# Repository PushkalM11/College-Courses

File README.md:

# College-Courses
Repository to store courses I have done at IIT Hyderabad during BTech.

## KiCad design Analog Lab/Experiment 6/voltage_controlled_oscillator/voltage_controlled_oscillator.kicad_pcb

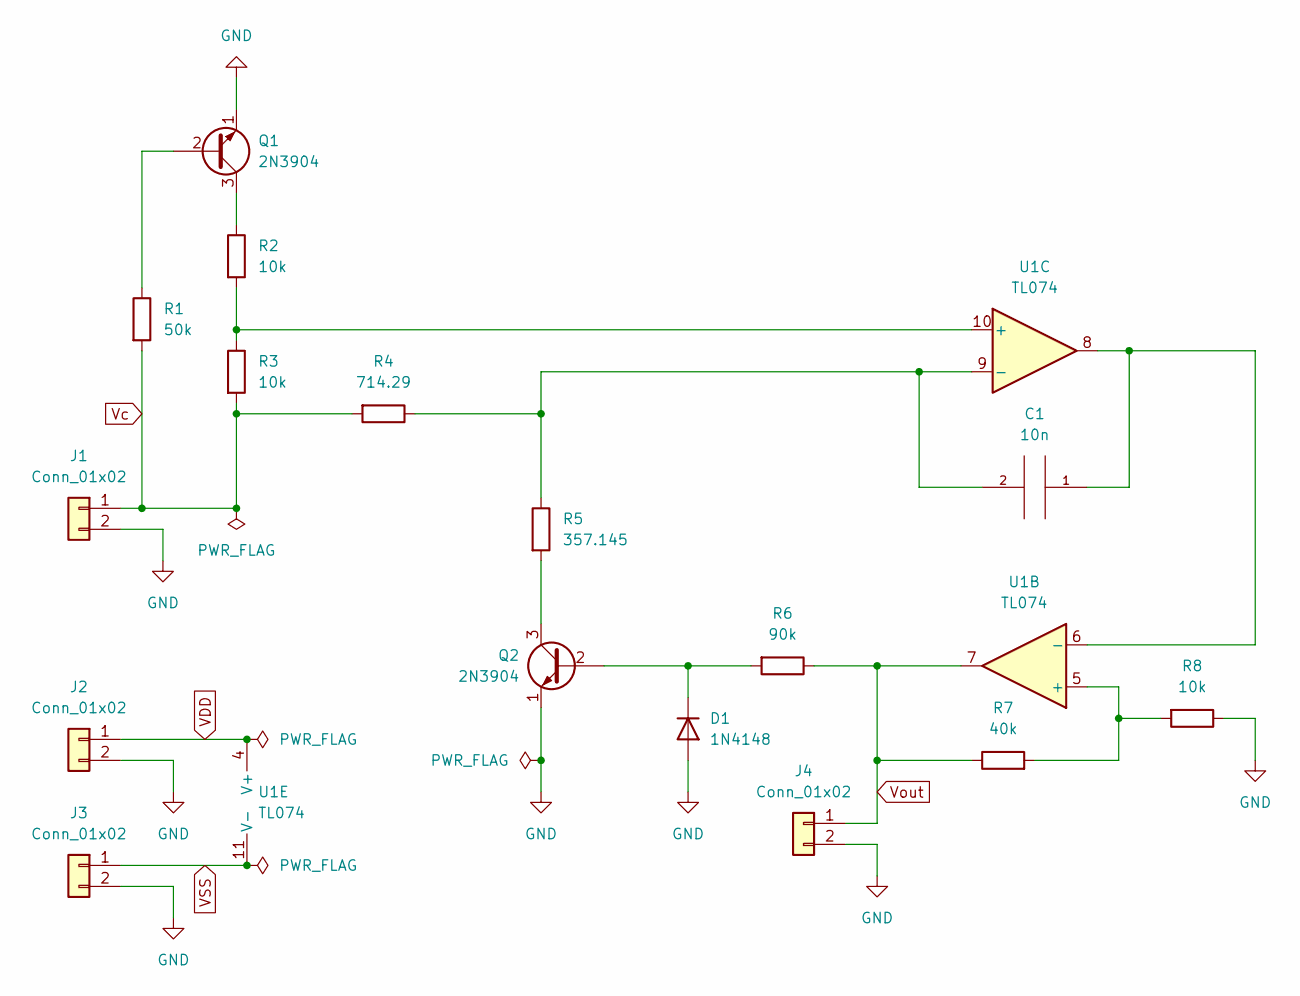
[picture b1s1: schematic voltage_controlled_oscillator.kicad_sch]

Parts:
C1: 10n; C_Disc_D3.4mm_W2.1mm_P2.50mm
D1: 1N4148; D_DO-35_SOD27_P7.62mm_Horizontal
J1, J2, J3, J4: Conn_01x02; Banana_Jack_2Pin
Q1, Q2: 2N3904; TO-92_Wide
R1: 50k; R_Axial_DIN0204_L3.6mm_D1.6mm_P1.90mm_Vertical
R2, R3, R8: 10k; R_Axial_DIN0204_L3.6mm_D1.6mm_P1.90mm_Vertical
R4: 714.29; R_Axial_DIN0204_L3.6mm_D1.6mm_P1.90mm_Vertical
R5: 357.145; R_Axial_DIN0204_L3.6mm_D1.6mm_P1.90mm_Vertical
R6: 90k; R_Axial_DIN0204_L3.6mm_D1.6mm_P1.90mm_Vertical
R7: 40k; R_Axial_DIN0204_L3.6mm_D1.6mm_P1.90mm_Vertical
U1: TL074; DIP-14_W7.62mm_LongPads

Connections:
GND: D1.2 (A), J1.2, J2.2, J3.2, J4.2, Q1.1 (E), Q2.1 (E), R8.1
unnamed: C1.1, U1.6 (-), U1.8
unnamed: C1.2, R4.1, R5.1, U1.9 (-)
unnamed: D1.1 (K), Q2.2 (B), R6.2
unnamed: Q1.2 (B), R1.1
unnamed: Q1.3 (C), R2.1
unnamed: Q2.3 (C), R5.2
unnamed: R2.2, R3.1, U1.10 (+)
unnamed: R7.2, R8.2, U1.5 (+)
VDD: J2.1, U1.4 (V+)
VSS: J3.1, U1.11 (V-)
Vc: J1.1, R1.2, R3.2, R4.2
Vout: J4.1, R6.1, R7.1, U1.7

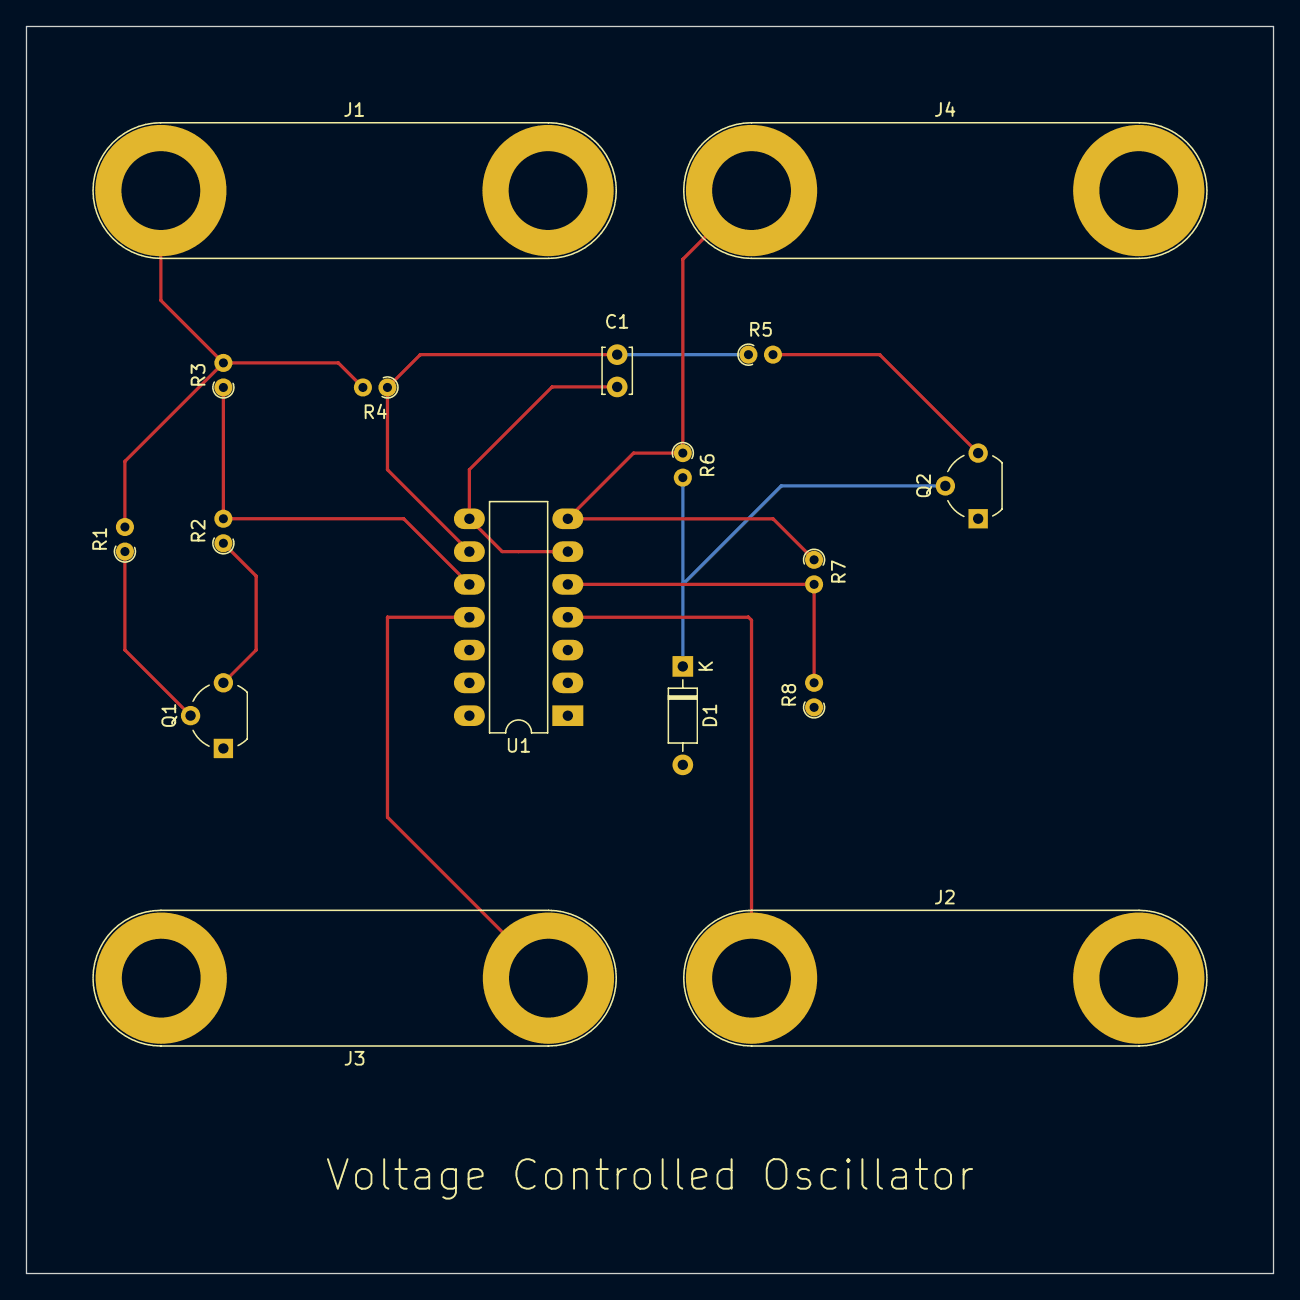
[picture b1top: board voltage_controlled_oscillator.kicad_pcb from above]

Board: 2 copper layers, 96.5 x 96.5 mm, 17 parts (0 on the bottom side), 13 nets.

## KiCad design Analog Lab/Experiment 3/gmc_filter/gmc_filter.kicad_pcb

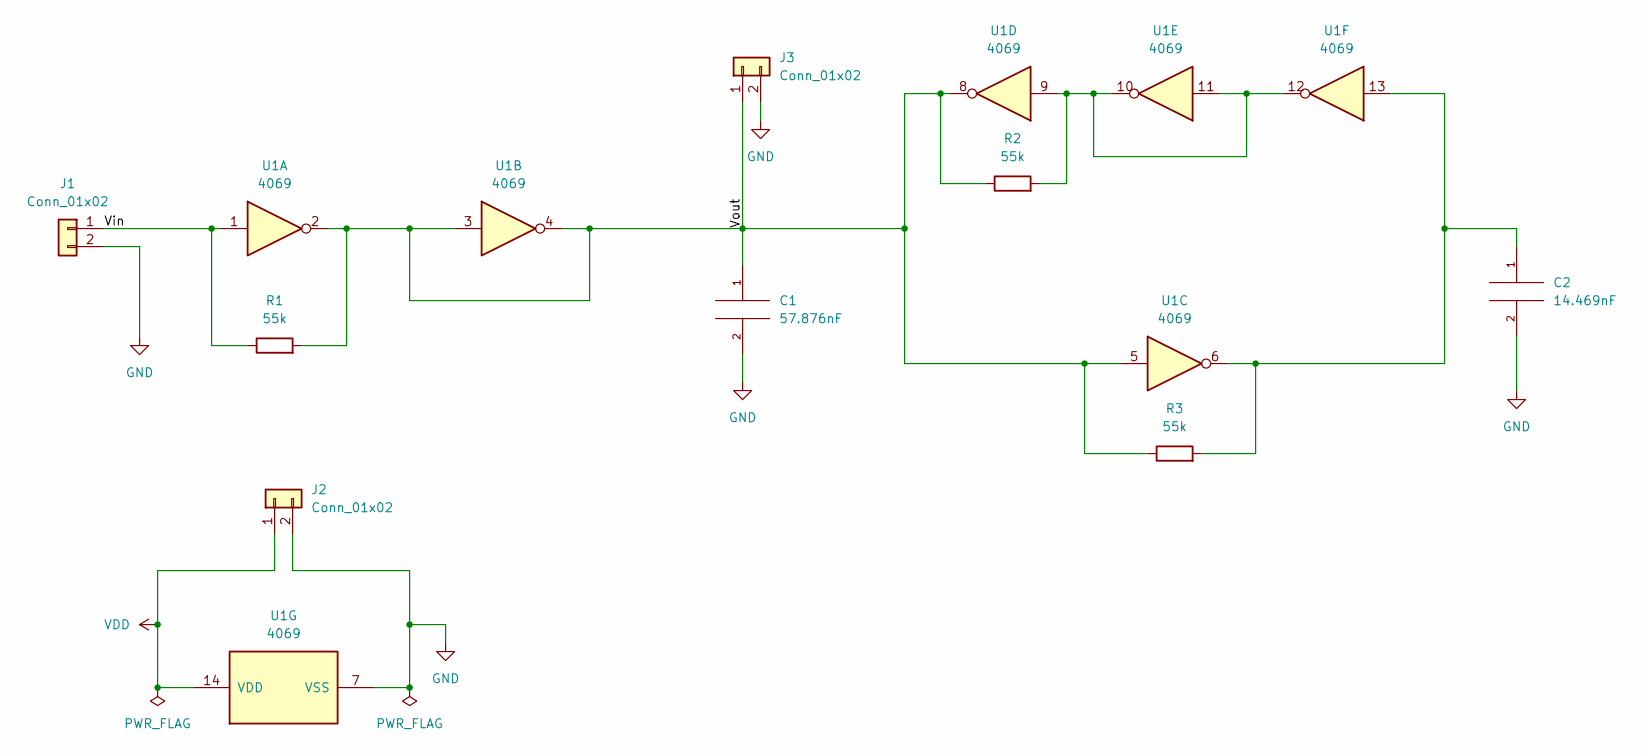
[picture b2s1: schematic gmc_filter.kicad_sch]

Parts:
C1: 57.876nF; C_Disc_D3.0mm_W1.6mm_P2.50mm
C2: 14.469nF; C_Disc_D3.0mm_W1.6mm_P2.50mm
J1, J2, J3: Conn_01x02; Banana_Jack_2Pin
R1, R2, R3: 55k; R_Axial_DIN0411_L9.9mm_D3.6mm_P5.08mm_Vertical
U1: 4069; DIP-14_W7.62mm

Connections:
/Vin: J1.1, R1.1, U1.1
/Vout: C1.1, J3.1, R1.2, R2.1, R3.1, U1.2, U1.3, U1.4, U1.5, U1.8
GND: C1.2, C2.2, J1.2, J2.2, J3.2, U1.7 (VSS)
unnamed: C2.1, R3.2, U1.6, U1.13
unnamed: R2.2, U1.9, U1.10, U1.11, U1.12
VDD: J2.1, U1.14 (VDD)

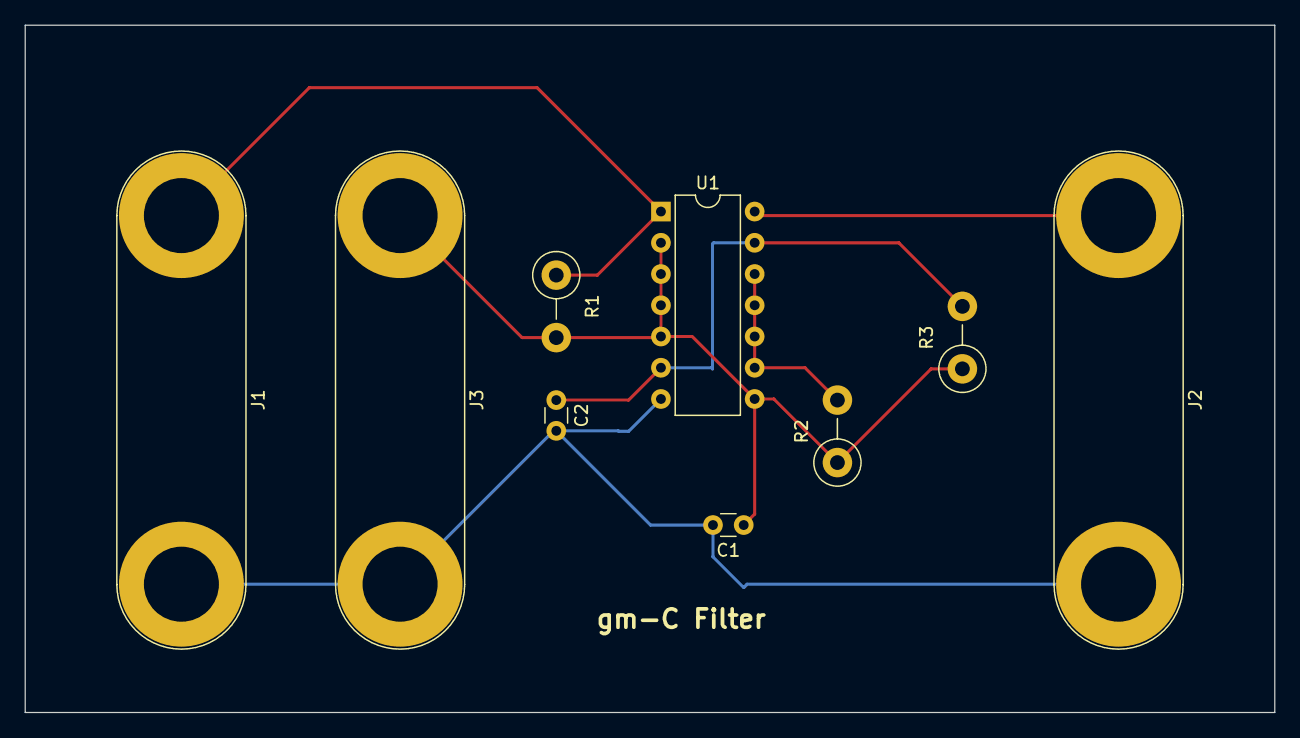
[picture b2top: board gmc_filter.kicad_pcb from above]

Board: 2 copper layers, 101.6 x 55.9 mm, 9 parts (0 on the bottom side), 6 nets.

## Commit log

2024-05-07 Final Project Code
2024-05-07 Removing .DS_Store
2024-05-07 Created .gitignore
